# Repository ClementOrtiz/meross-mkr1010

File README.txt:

Source codes are provided in "src" folder.

Documentations, Kicad shematics and photos are provided within "doc" folder.

The program named SCS.ino aims to remotly control a connected Outlet plug in order to switch it ON or OFF, check the wiki for more details. 

It has to be incorporated into the SCS Project "Smart Cooking System" made by Régis Leruste.

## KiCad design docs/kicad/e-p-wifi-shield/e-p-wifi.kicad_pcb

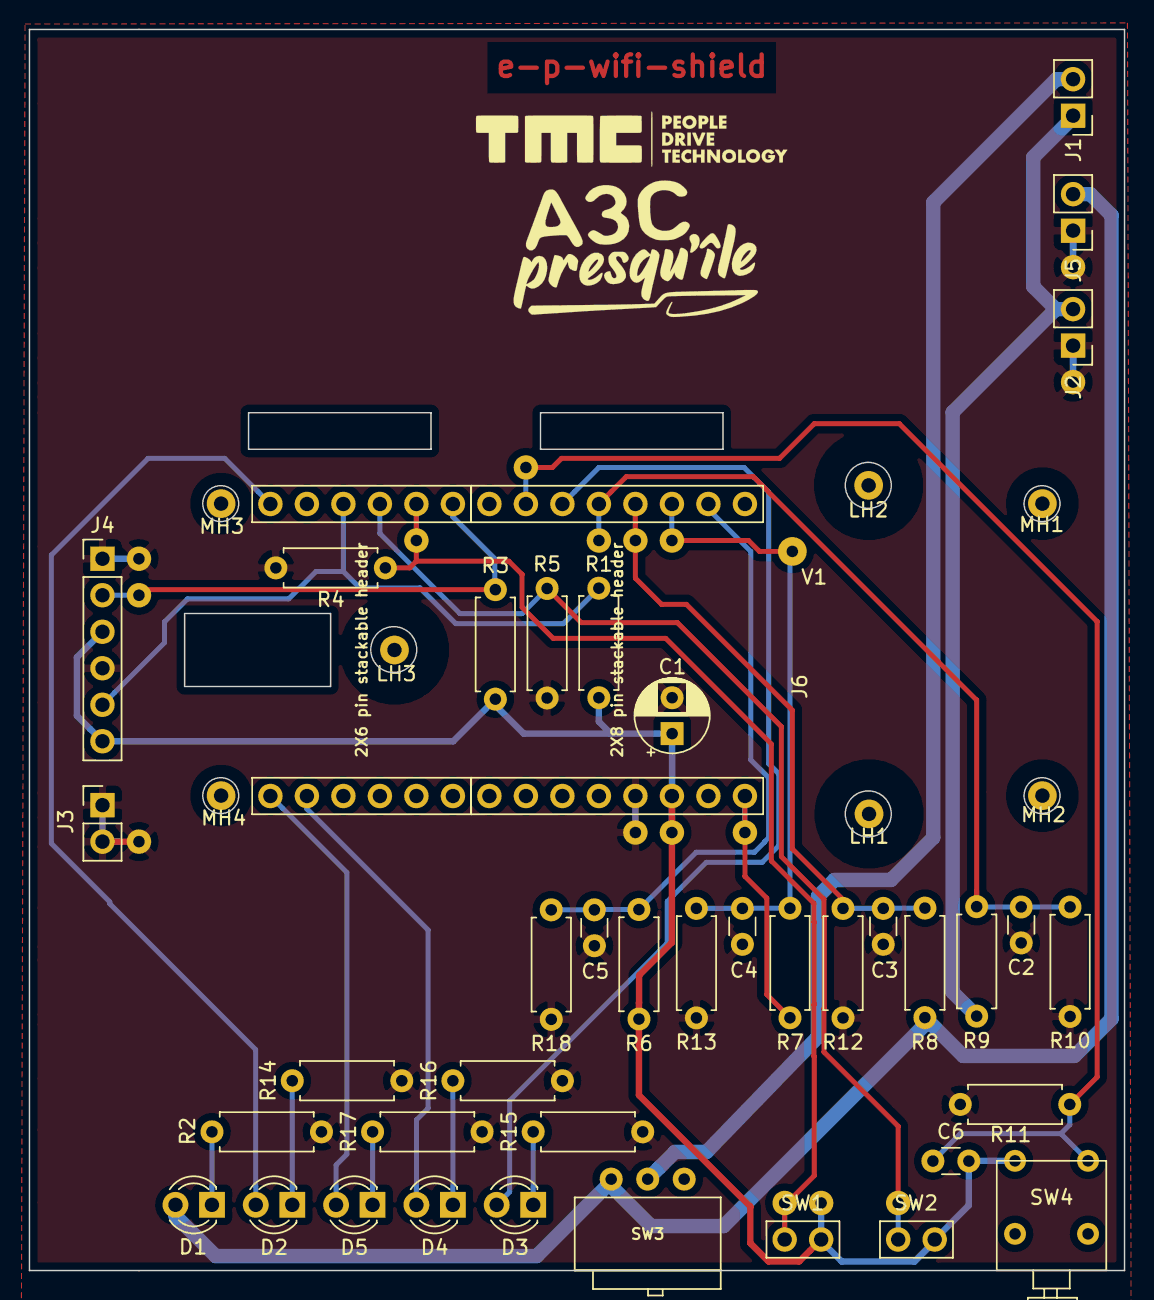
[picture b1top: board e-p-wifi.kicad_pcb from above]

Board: 2 copper layers, 76.2 x 86.4 mm, 47 parts (0 on the bottom side), 24 nets.

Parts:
C1: 4.7µF; CP_Radial_D5.0mm_P2.50mm
C2, C3, C4, C5, C6: 0.1mF; C_Disc_D3.0mm_W1.6mm_P2.50mm
D1: vert; LED_D3.0mm
D2: Vert; LED_D3.0mm
D3: bleu; LED_D3.0mm
D4: Rouge; LED_D3.0mm
D5: Jaune; LED_D3.0mm
J1: Shunt; PinHeader_1x02_P2.54mm_Vertical
J2: Vbat1; PinHeader_1x02_P2.54mm_Vertical
J3: Masse T1; PinHeader_1x02_P2.54mm_Vertical
J4: Température; PinHeader_1x06_P2.54mm_Vertical_J4
J5: Vbat2; PinHeader_1x02_P2.54mm_Vertical
J6: Conn_02x14_MKR1010; PinSocket_2x14_MKR1010_ov
LH1, LH2, LH3: Via-DIY
MH1, MH2, MH3, MH4: Via-DIY
R1, R3, R6, R7, R8, R9, R10, R12, R13, R18: 4.7k; R_Axial_DIN0207_L6.3mm_D2.5mm_P7.62mm_Horizontal
R2, R14, R15, R16, R17: 1K; R_Axial_DIN0207_L6.3mm_D2.5mm_P7.62mm_Horizontal
R4, R5, R11: 47k; R_Axial_DIN0207_L6.3mm_D2.5mm_P7.62mm_Horizontal
SW1: StSp - Farnell 986-501; jumper-switch-sw1
SW2: Sleep - Farnell 986-501; jumper-switch-sw2
SW3: Conrad 711771; switch
SW4: BP APEM - Farnell 108-2512; BP
V1: Via; Via-DIY

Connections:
+3V3: C1.1, C6.2, J4.3, J4.6, J6.14, J6.+3V3, R1.1, R3.1, R6.1, SW1.1, SW1.4, SW2.1, SW4.1
GND: C1.2, C2.2, C3.2, C4.2, C5.2, J2.1, J2.3, J3.1, J3.2, J3.3, J4.1, J4.4, J4.8, J5.1, J5.3, J6.13, J6.GND, R2.1, R4.2, R5.2, R10.2, R11.1, R12.2, R13.2, R14.1, R15.1, R16.1, R17.1, R18.2
unnamed: C2.1, J6.10, J6.A3, R9.2, R10.1
unnamed: C3.1, J6.11, J6.A2, R8.2, R12.1
unnamed: C4.1, J6.12, J6.A1, R7.2, R13.1, V1.1
unnamed: C5.1, J6.A0, R6.2, R18.1
unnamed: C6.1, J6.9, J6.A5, R11.2, SW4.2
unnamed: D1.1, R2.2
unnamed: D1.2, J5.2, R8.1, SW3.3
unnamed: D2.1, R14.2
unnamed: D2.2, J6.D5
unnamed: D3.1, R15.2
unnamed: D3.2, J6.A4
unnamed: D4.1, R16.2
unnamed: D4.2, J6.D7
unnamed: D5.1, R17.2
unnamed: D5.2, J6.D6
unnamed: J1.1, J2.2, R9.1
unnamed: J1.2, SW3.2
unnamed: J4.2, J4.7, J6.D0, R3.2
unnamed: J4.5, J6.D3, R1.2
unnamed: J6.15, J6.+5V, R7.1
unnamed: J6.8, J6.D1, R4.1, SW1.2, SW1.3
unnamed: J6.D2, R5.1, SW2.2, SW2.4

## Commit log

2020-03-05 initialising repo with Mickael work
2020-03-06 Little refactor, no fonctionnal change
2020-03-06 adding sniffed frame dump example
2020-03-06 Starting new project on 'search for plug and auto ip detection' subject
2020-03-06 Base of new Wifi project
2020-03-10 Implementation of a scaner that ping then launch a query on responding host
2020-03-10 Adding fonctionnality on WiFiNINA lib for connection timeout
2020-03-10 previous commit error
2020-03-10 adding modified WiFiNINA lib
2020-03-10 for information, WiFiNINA timeout failed
2020-03-10 Use of hostByName instead of searching arround the local network
2020-03-11 New software version with embedded library
2020-03-11 First version of WifiInterrupt lib
2020-03-12 Adding WifiTools
2020-03-12 Fonctionnal lib externalisation
2020-03-12 refacto
2020-03-13 Integrating hostByName in WifiTools lib
2020-03-13 Wrinting Header description
2020-03-13 removing lack of code during EEPROM test
2020-03-13 externalizing Waiting Time for IP research retry
2020-04-01 removing used of PIN 6 to power up button
2020-04-03 Adding arduino-cli installationscript
2020-04-06 Modification's on new Wifi and Frame
2020-04-06 Refactor of AppToken in From field and changing it integration
2020-04-07 Conditionnal waiting for user to connect to serial port
2020-04-07 adding lib
2020-04-08 SoftUnbouncedButton tested
2020-04-08 adding pictures to repo
2020-04-08 Adding CC Logo on pictures
2020-04-08 update code lines pictures
2020-04-08 Adding CC and Headers
2020-04-08 Adding readme
2020-04-08 Readme
2020-04-08 Integrating SoftUnbouncedButton library tot SCS.ino
2020-04-14 PB schema
2020-04-14 Modifying Copyrigth to License
2020-04-14 adding Serial Journalizer prototype
2020-04-23 Reorganisation and pcb modification
2020-04-23 adding SCS schematics
2020-04-27 Modifications on pcb
2020-04-27 Modifiyng schematics
2020-04-27 Anonymizing Wifi informations
2020-04-27 Adding code captures
2020-04-27 capture modifications
2020-04-28 adding sequence diagramm for SCS.ino source
2020-04-28 modif pcb
2020-04-29 adding SCS.ino modelisation and solder layer csv
2020-04-29 adding activity diagram
2020-04-29 cleaning Kicad Project and adding base for none vias pcb
2020-04-29 create none via pcb
2020-04-29 updating massplan
2020-04-30 adding schema
2020-04-30 schema for getUnbouncedState
2020-04-30 schema for getSwitchState
2020-04-30 update schema and pcb without via
2020-04-30 rename 'sans_via' files
2020-05-04 All libs in one file
2020-05-05 modifying file names with b_
2020-05-05 adding new project
2020-05-05 modifying lib for more even simplicity
2020-05-08 adding pictures
